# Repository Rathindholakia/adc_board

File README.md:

# adc_board

This is a CadSoft Eagle project of an ADC board using AD7864 for sensing analog input and to interface it with EMIFA of TI OMAP-L137.

Description:

Two AD7864-1 are used for +-10 Vac input

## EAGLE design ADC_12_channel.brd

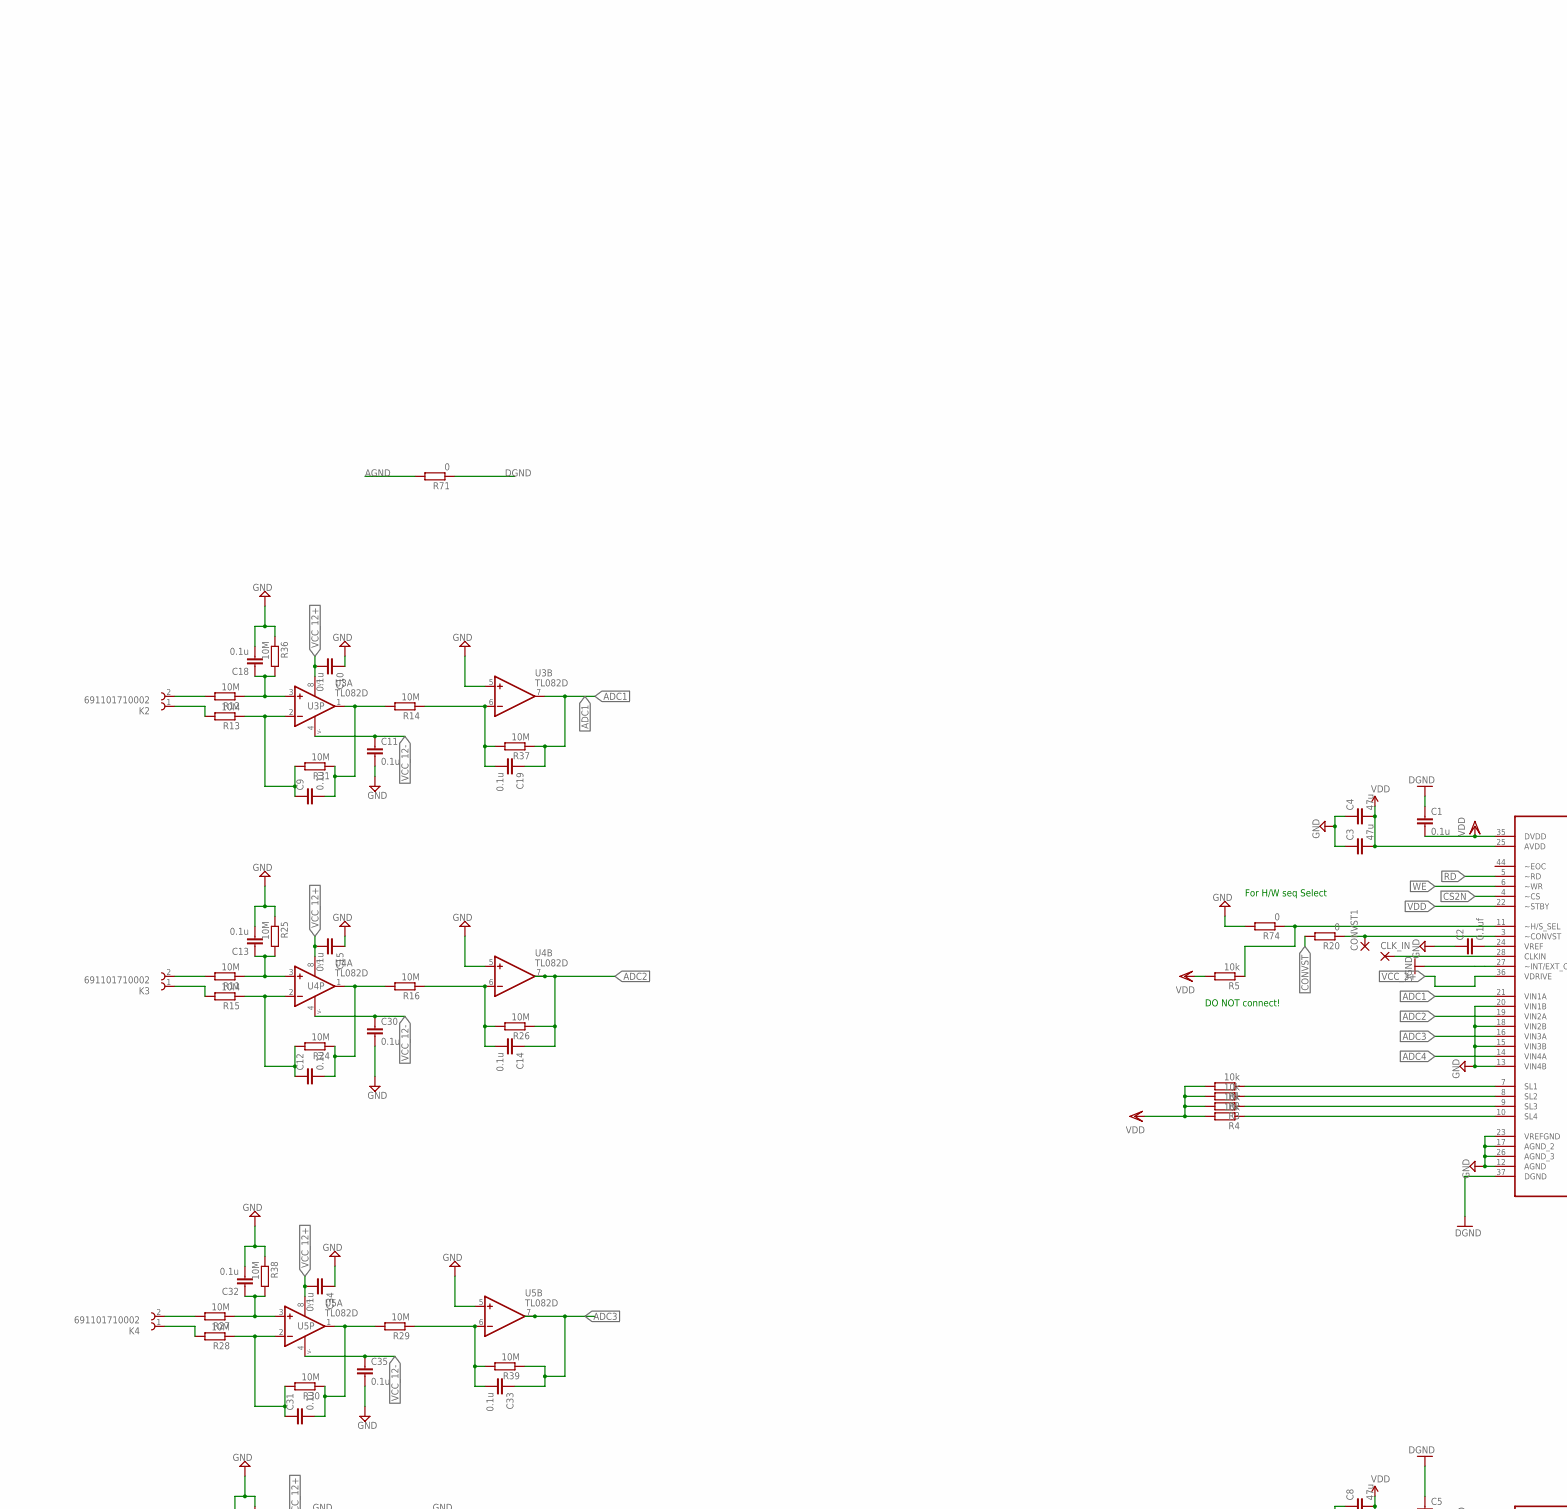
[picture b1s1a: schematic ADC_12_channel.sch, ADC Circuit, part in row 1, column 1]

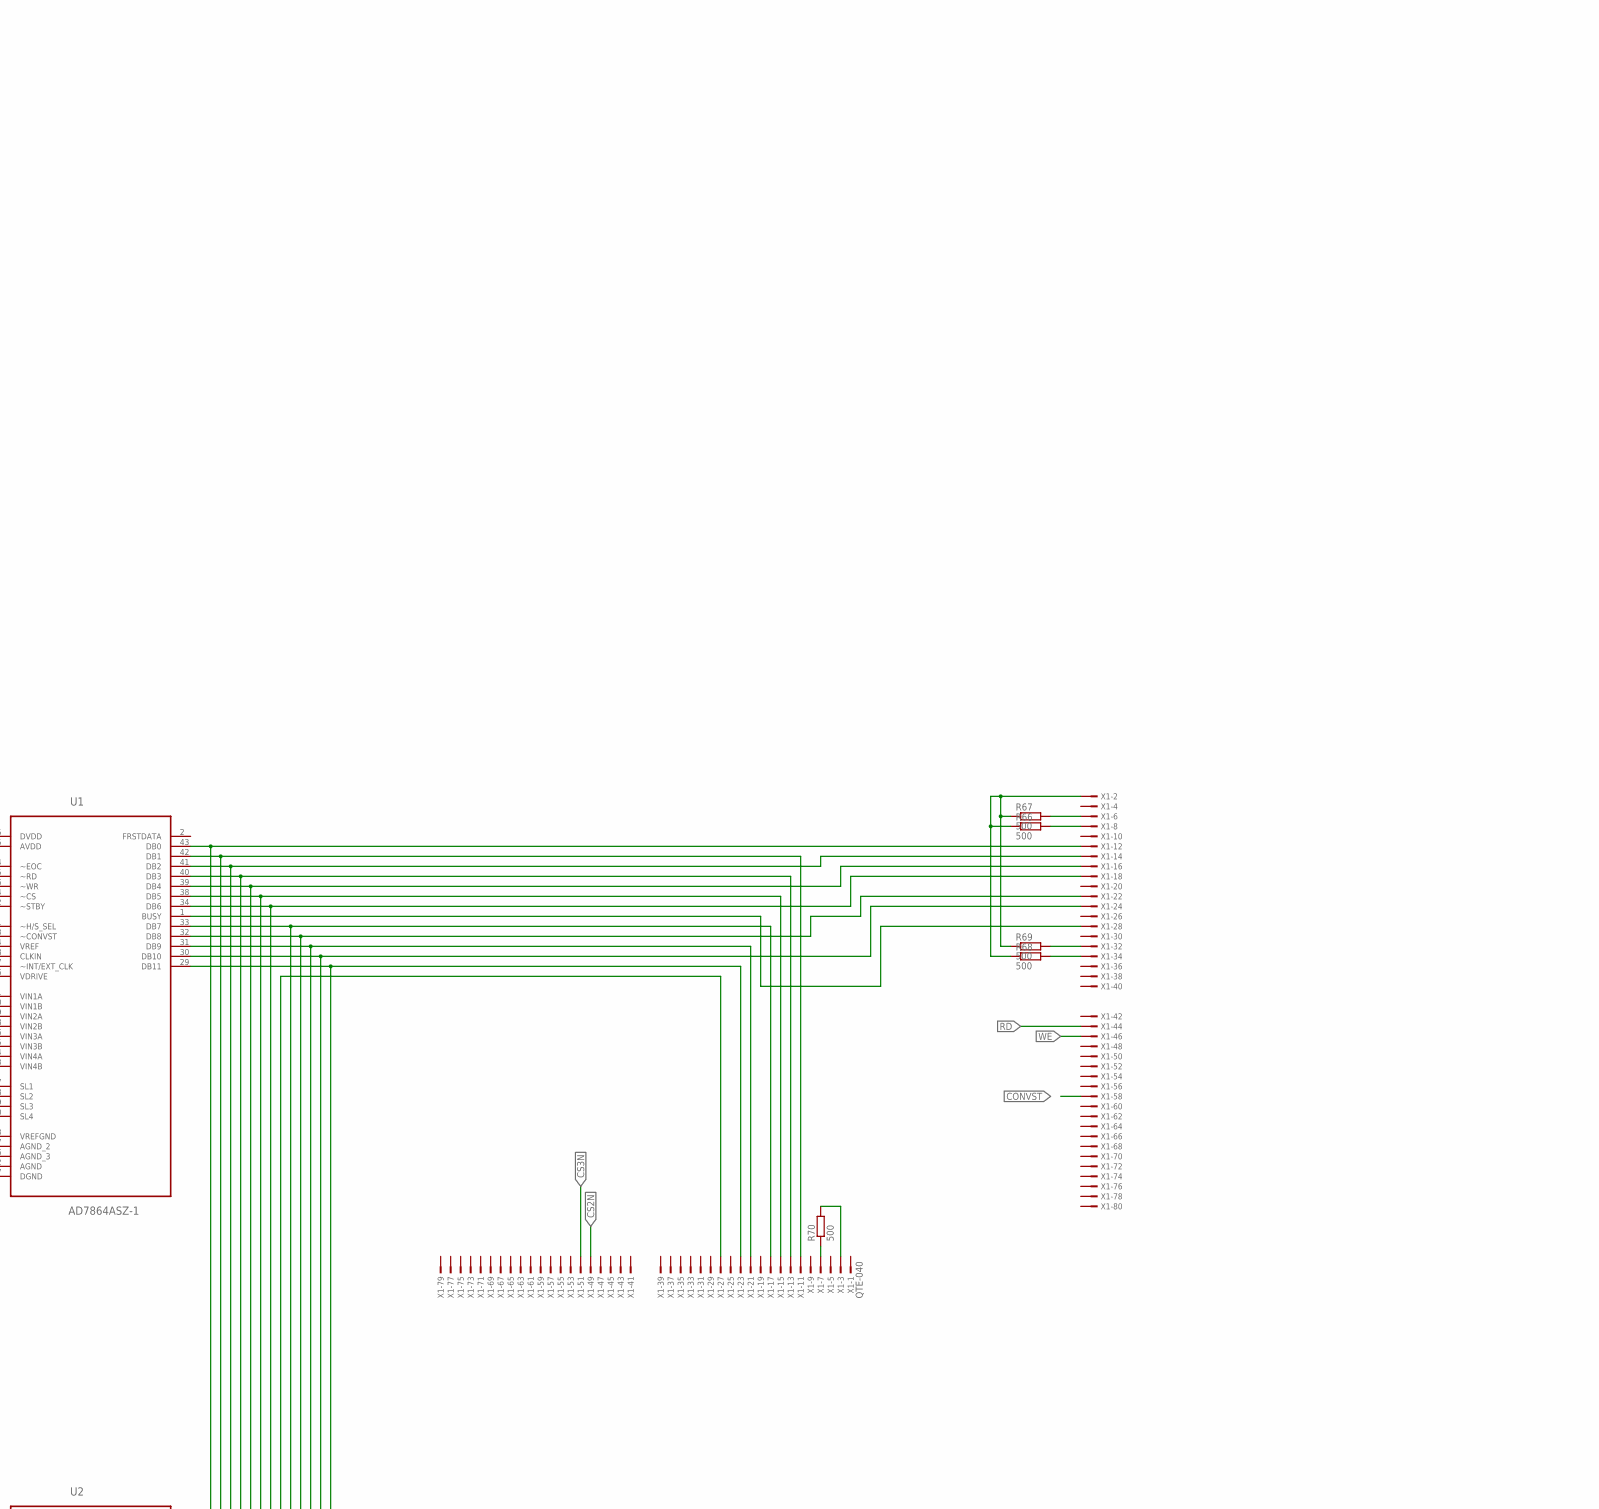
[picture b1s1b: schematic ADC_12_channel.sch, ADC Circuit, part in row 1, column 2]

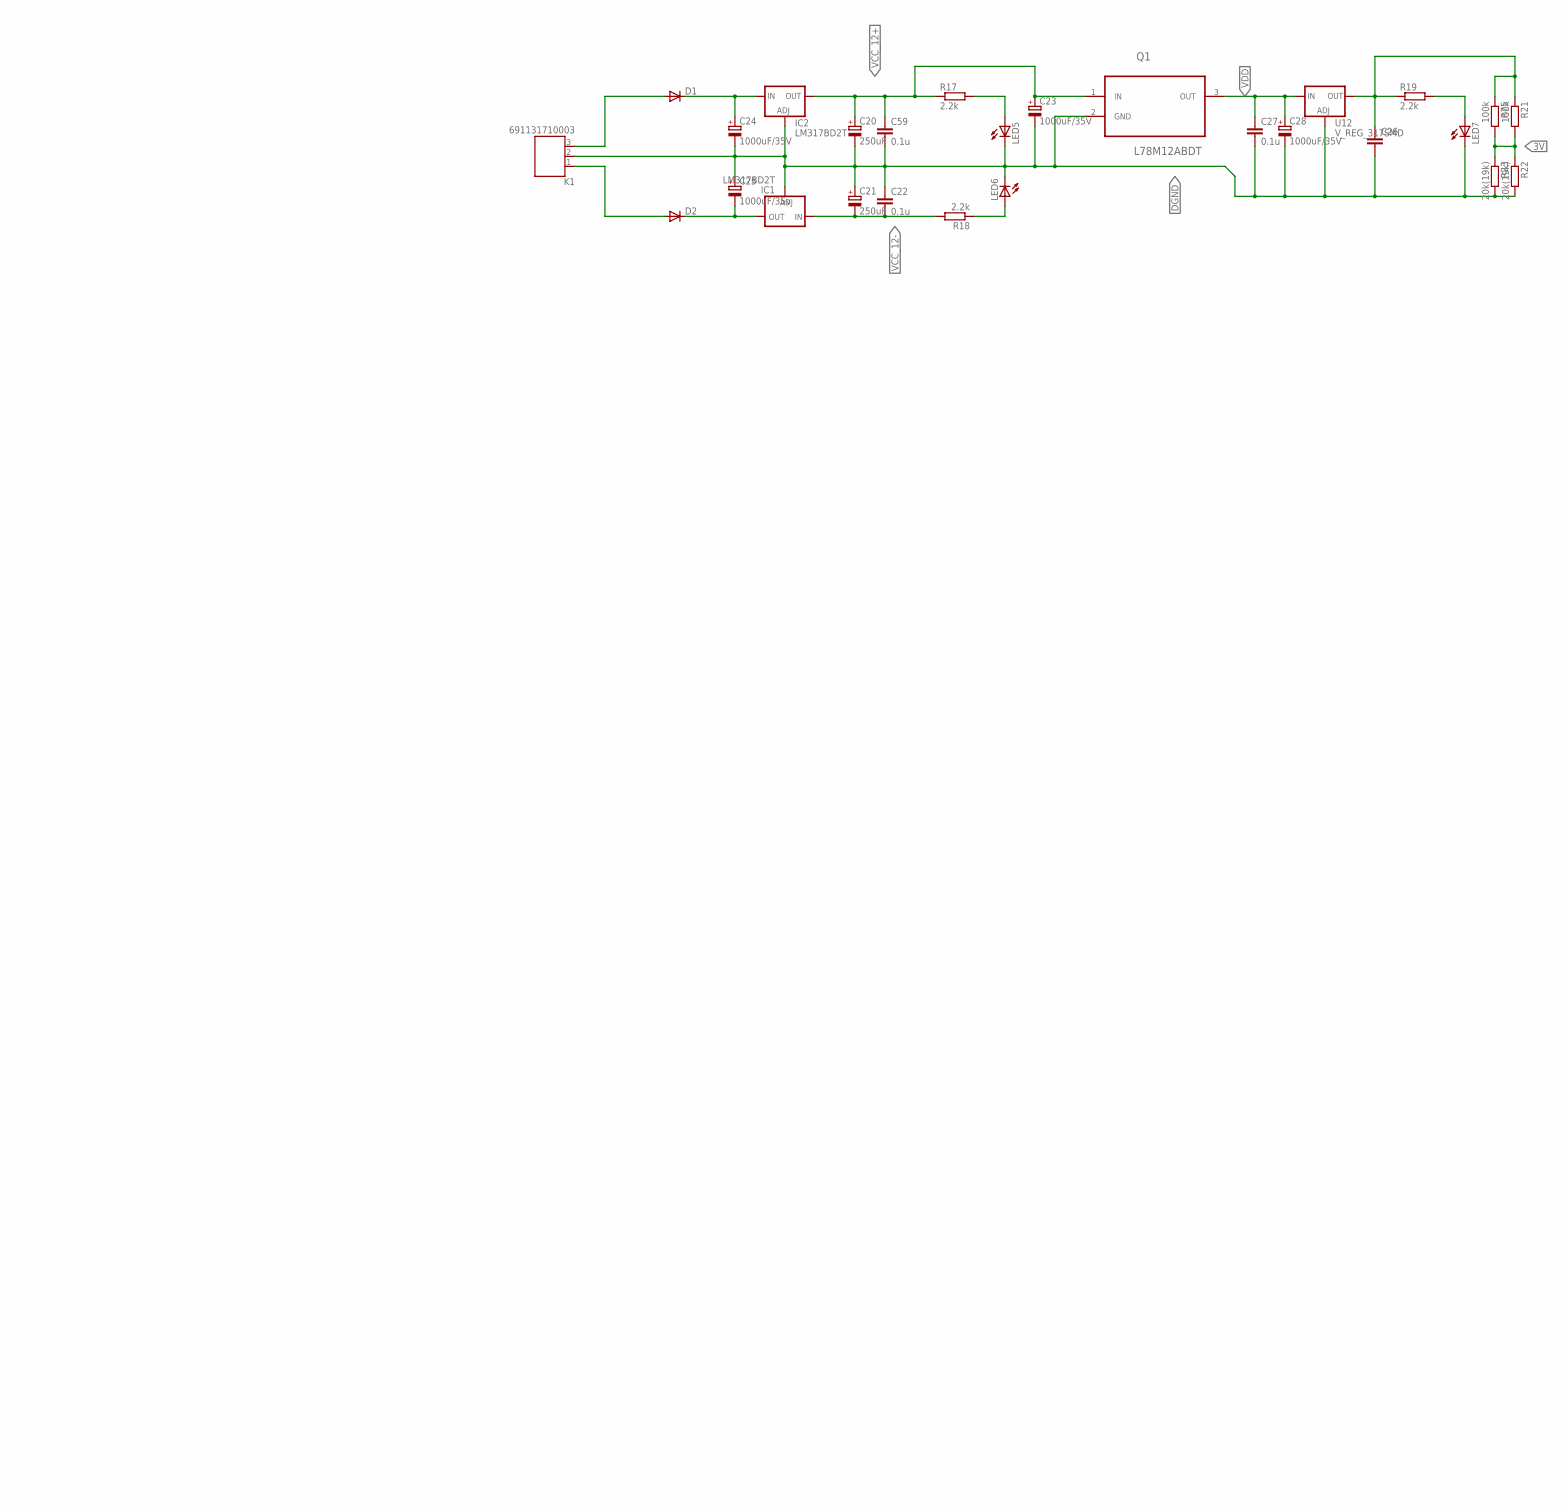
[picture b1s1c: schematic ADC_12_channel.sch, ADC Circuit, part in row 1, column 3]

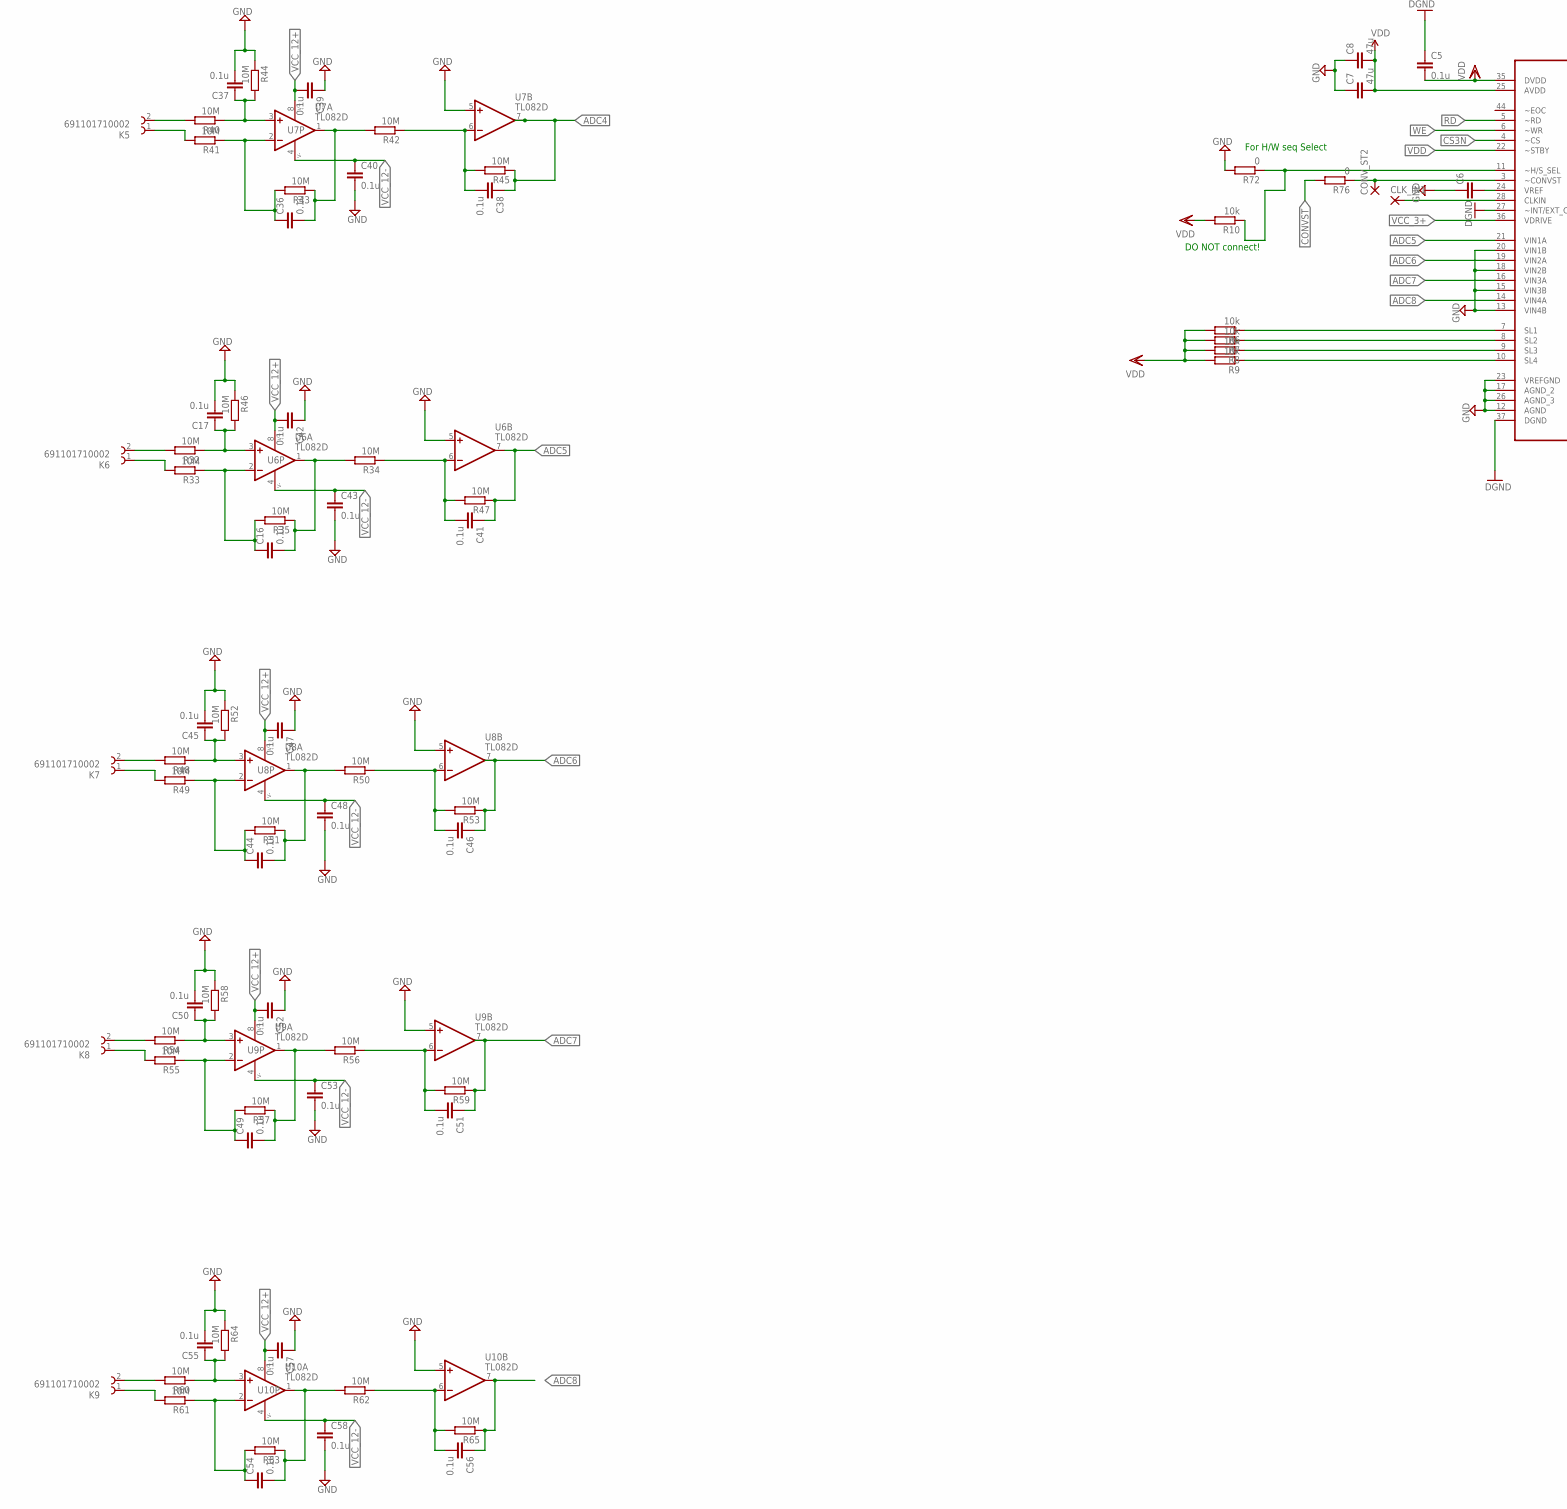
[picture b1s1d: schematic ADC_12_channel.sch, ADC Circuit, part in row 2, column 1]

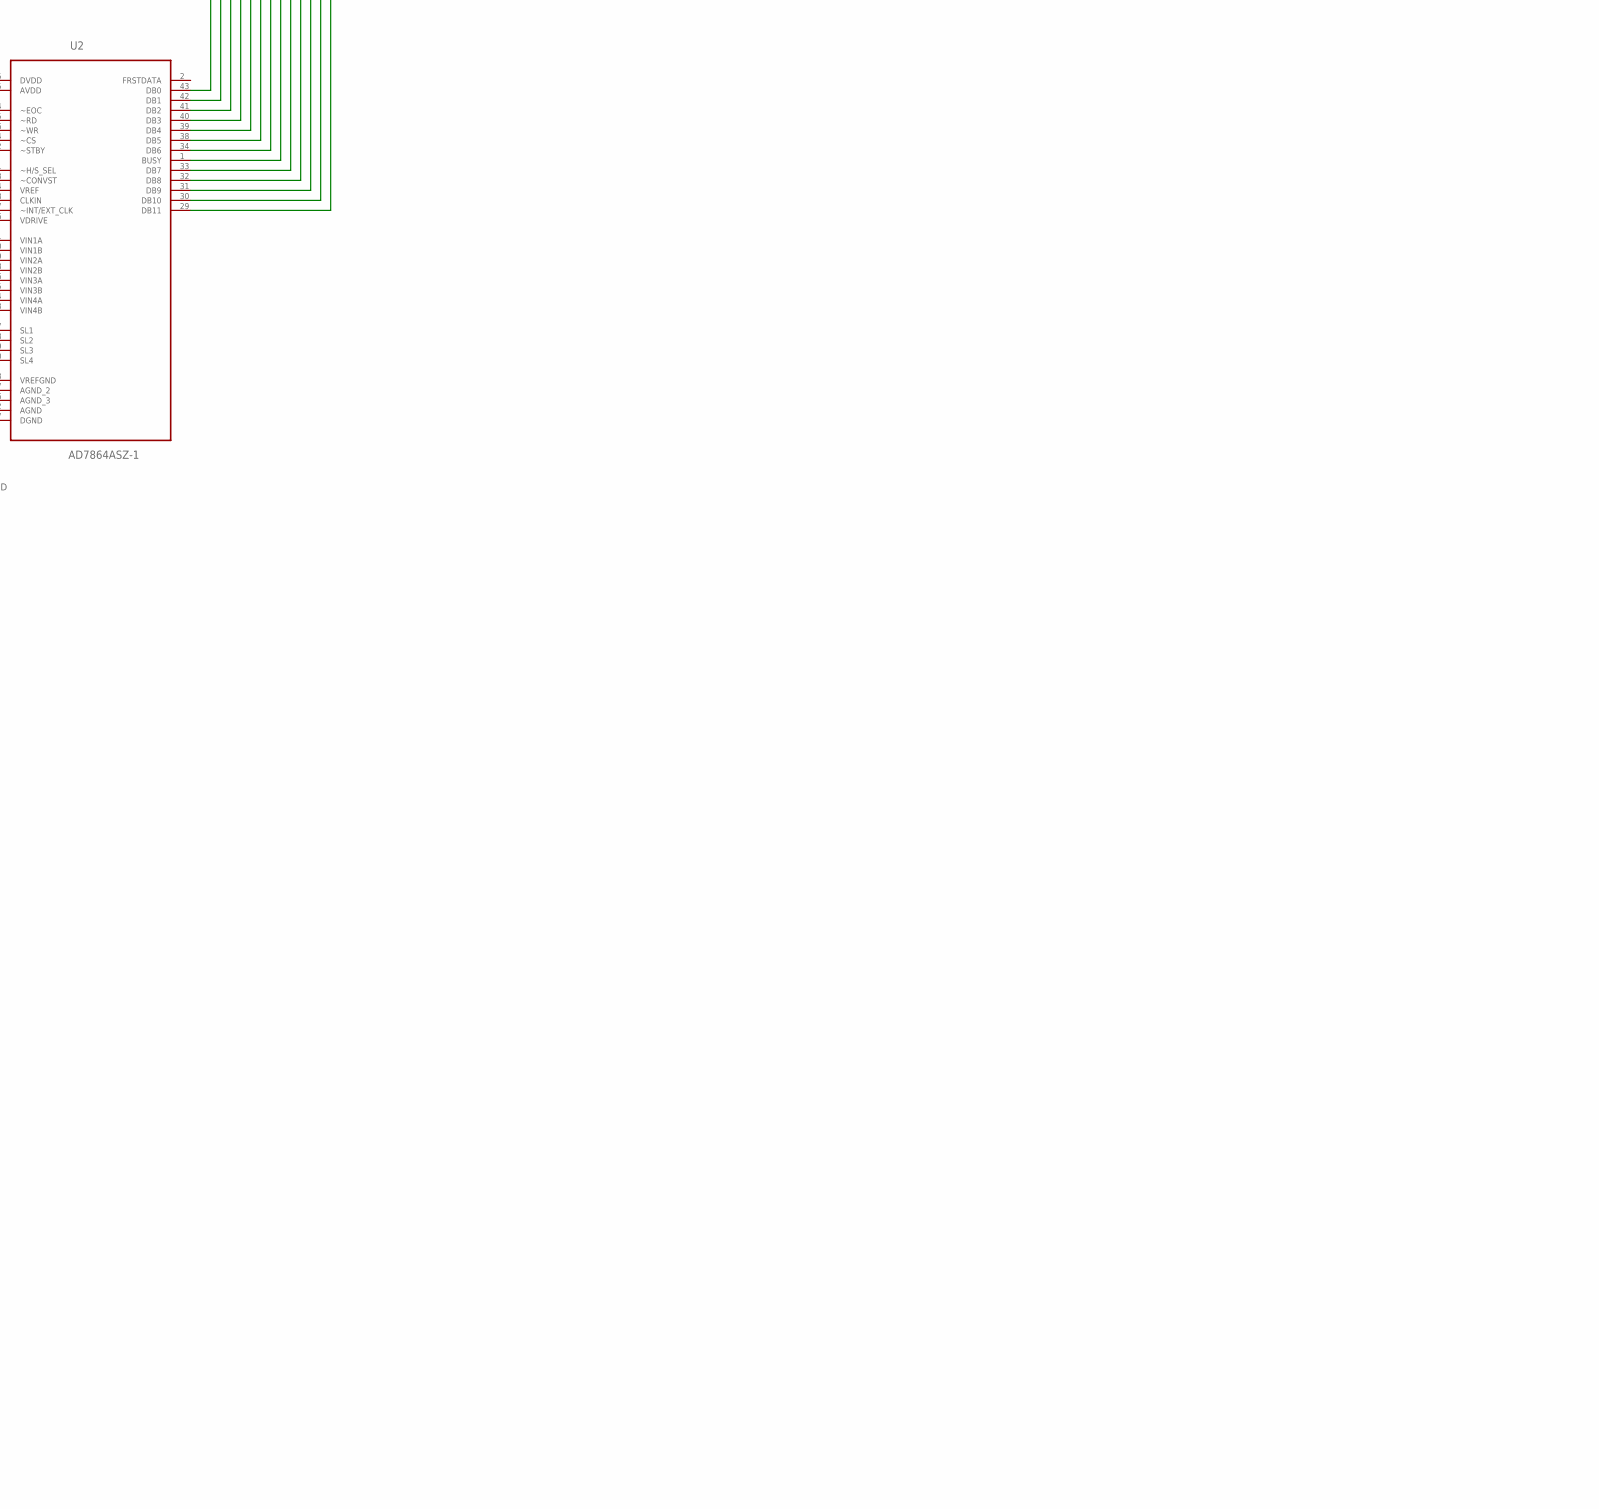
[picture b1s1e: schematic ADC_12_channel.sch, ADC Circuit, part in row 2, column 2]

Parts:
C1, C5, C9, C10, C11, C12, C13, C14, C15, C16, C17, C18, C19, C22, C27, C30, C31, C32, C33, C34, C35, C36, C37, C38, C39, C40, C41, C42, C43, C44, C45, C46, C47, C48, C49, C50, C51, C52, C53, C54, C55, C56, C57, C58, C59: 0.1u; C0603K
C2: 0.1uf; C0603K
C3, C4, C7, C8: 47u; C1206K
C6: C-EUC0603K; C0603K
C20, C21: 250uF; E5-10,5
C23, C24, C28: 1000uF/35V; E5-10,5
C25: 1000uF/35v; E5-10,5
C26: C-EUC1206K; C1206K
CLK_IN, CLK_IN1: 3,17/1,3
CONVST1: 3,17/1,3
CONV_ST2: 3,17/1,3
D1, D2: DIODE-DO-214AC; DO-214AC
IC1, IC2: LM317BD2T; D2PACK
K1: 691131710003
K2, K3, K4, K5, K6, K7, K8, K9: 691101710002
LED5: LEDSML1206; SML1206
LED6, LED7: LEDSMT1206; 1206
Q1: L78M12ABDT; TO225P972X240-3N
R1, R2, R3, R4, R5, R6, R7, R8, R9, R10: 10k; M1206
R11, R12, R13, R14, R15, R16, R24, R25, R26, R27, R28, R29, R30, R31, R32, R33, R34, R35, R36, R37, R38, R39, R40, R41, R42, R43, R44, R45, R47, R48, R49, R50, R51, R53, R54, R55, R56, R57, R59, R60, R61, R62, R63, R64, R65: 10M; M1206
R17, R18, R19: 2.2k; R1206
R20, R71, R72, R74, R76: 0; M1206
R21, R75: 100k; R1206
R22, R23: 20k(19k); R1206
R46, R52, R58: 10M; M0805
R66, R67, R68, R69, R70: 500; M1206
U1, U2: AD7864ASZ-1; QFP80P1390X1390X245-44N
U3, U4, U5, U6, U7, U8, U9, U10: TL082D; SO08
U12: V_REG_317SMD; SOT223
X1: QTE-040

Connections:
3V: R21.2, R22.1, R23.1, R75.2
ADC1: C19.1, R37.1, U1.21 (VIN1A), U3.7 (OUT)
ADC2: C14.1, R26.1, U1.19 (VIN2A), U4.7 (OUT)
ADC3: C33.1, R39.1, U1.16 (VIN3A), U5.7 (OUT)
ADC4: C38.1, R45.1, U1.14 (VIN4A), U7.7 (OUT)
ADC5: C41.1, R47.1, U2.21 (VIN1A), U6.7 (OUT)
ADC6: C46.1, R53.1, U2.19 (VIN2A), U8.7 (OUT)
ADC7: C51.1, R59.1, U2.16 (VIN3A), U9.7 (OUT)
ADC8: C56.1, R65.1, U2.14 (VIN4A), U10.7 (OUT)
AGND: C2.1, C3.1, C4.1, C6.1, C7.1, C8.1, C13.2, C17.2, C18.2, C32.2, C37.2, C45.2, C50.2, C55.2, R25.1, R36.1, R38.1, R44.1, R46.1, R52.1, R58.1, R64.1, R71.2, U1.12 (AGND), U1.13 (VIN4B), U1.15 (VIN3B), U1.17 (AGND_2), U1.18 (VIN2B), U1.20 (VIN1B), U1.23 (VREFGND), U1.26 (AGND_3), U2.12 (AGND), U2.13 (VIN4B), U2.15 (VIN3B), U2.17 (AGND_2), U2.18 (VIN2B), U2.20 (VIN1B), U2.23 (VREFGND), U2.26 (AGND_3), U3.5 (+IN), U4.5 (+IN), U5.5 (+IN), U6.5 (+IN), U7.5 (+IN), U8.5 (+IN), U9.5 (+IN), U10.5 (+IN)
CONVST: R20.2, R76.2, X1.58
CS2N: U1.4 (~CS), X1.49
CS3N: U2.4 (~CS), X1.51
DGND: C1.1, C5.1, C10.1, C11.2, C15.1, C20.-, C21.+, C22.1, C23.-, C24.-, C25.+, C26.2, C27.2, C28.-, C30.2, C34.1, C35.2, C39.1, C40.2, C42.1, C43.2, C47.1, C48.2, C52.1, C53.2, C57.1, C58.2, C59.2, IC1.1 (ADJ), IC2.1 (ADJ), K1.2, LED5.C, LED6.C, LED7.C, Q1.2 (GND), R22.2, R23.2, R71.1, R72.2, R74.2, U1.27 (~INT/EXT_CLK), U1.37 (DGND), U2.27 (~INT/EXT_CLK), U2.37 (DGND), U12.1 (ADJ)
unnamed: U1.43 (DB0), U2.43 (DB0), X1.12
unnamed: C9.1, R13.1, R31.2, U3.2 (-IN)
unnamed: U1.41 (DB2), U2.41 (DB2), X1.14
unnamed: U1.39 (DB4), U2.39 (DB4), X1.16
unnamed: U1.34 (DB6), U2.34 (DB6), X1.18
unnamed: U1.32 (DB8), U2.32 (DB8), X1.22
unnamed: U1.30 (DB10), U2.30 (DB10), X1.24
unnamed: U1.40 (DB3), U2.40 (DB3), X1.13
unnamed: U1.38 (DB5), U2.38 (DB5), X1.15
unnamed: U1.33 (DB7), U2.33 (DB7), X1.17
unnamed: CLK_IN.1, U1.28 (CLKIN)
unnamed: U1.29 (DB11), U2.29 (DB11), X1.23
unnamed: R4.1, U1.10 (SL4)
unnamed: R3.1, U1.9 (SL3)
unnamed: R2.1, U1.8 (SL2)
unnamed: C2.2, U1.24 (VREF)
unnamed: R1.1, U1.7 (SL1)
unnamed: CONVST1.1, R20.1, U1.3 (~CONVST)
unnamed: R5.1, R74.1, U1.11 (~H/S_SEL)
unnamed: R9.1, U2.10 (SL4)
unnamed: R8.1, U2.9 (SL3)
unnamed: R7.1, U2.8 (SL2)
unnamed: R6.1, U2.7 (SL1)
unnamed: C6.2, U2.24 (VREF)
unnamed: CONV_ST2.1, R76.1, U2.3 (~CONVST)
unnamed: R10.1, R72.1, U2.11 (~H/S_SEL)
unnamed: U1.42 (DB1), U2.42 (DB1), X1.11
unnamed: K3.2, R11.2
unnamed: C19.2, R14.1, R37.2, U3.6 (-IN)
unnamed: U1.31 (DB9), U2.31 (DB9), X1.21
unnamed: K3.1, R15.2
unnamed: K2.1, R13.2
unnamed: C12.1, R15.1, R24.2, U4.2 (-IN)
unnamed: C12.2, R16.2, R24.1, U4.1 (OUT)
unnamed: C25.-, D2.C, IC1.3 (OUT)
unnamed: C24.+, D1.C, IC2.2 (IN)
unnamed: LED5.A, R17.2
unnamed: LED6.A, R18.1
unnamed: D1.A, K1.3
unnamed: D2.A, K1.1
unnamed: LED7.A, R19.2
unnamed: K6.2, R32.2
unnamed: K6.1, R33.2
unnamed: C13.1, R11.1, R25.2, U4.3 (+IN)
unnamed: C14.2, R16.1, R26.2, U4.6 (-IN)
unnamed: CLK_IN1.1, U2.28 (CLKIN)
unnamed: U1.1 (BUSY), X1.28
unnamed: U2.1 (BUSY), X1.27
unnamed: K4.2, R27.2
unnamed: K2.2, R12.2
unnamed: C18.1, R12.1, R36.2, U3.3 (+IN)
unnamed: C9.2, R14.2, R31.1, U3.1 (OUT)
unnamed: K4.1, R28.2
unnamed: C31.1, R28.1, R30.2, U5.2 (-IN)
unnamed: C31.2, R29.2, R30.1, U5.1 (OUT)
unnamed: C32.1, R27.1, R38.2, U5.3 (+IN)
unnamed: C16.1, R33.1, R35.2, U6.2 (-IN)
unnamed: C16.2, R34.2, R35.1, U6.1 (OUT)
unnamed: C17.1, R32.1, R46.2, U6.3 (+IN)
unnamed: C41.2, R34.1, R47.2, U6.6 (-IN)
unnamed: C33.2, R29.1, R39.2, U5.6 (-IN)
unnamed: K5.2, R40.2
unnamed: K5.1, R41.2
unnamed: C36.1, R41.1, R43.2, U7.2 (-IN)
unnamed: C36.2, R42.2, R43.1, U7.1 (OUT)
unnamed: C37.1, R40.1, R44.2, U7.3 (+IN)
unnamed: C38.2, R42.1, R45.2, U7.6 (-IN)
unnamed: K7.2, R48.2
unnamed: K7.1, R49.2
unnamed: C44.1, R49.1, R51.2, U8.2 (-IN)
unnamed: C44.2, R50.2, R51.1, U8.1 (OUT)
unnamed: C45.1, R48.1, R52.2, U8.3 (+IN)
unnamed: C46.2, R50.1, R53.2, U8.6 (-IN)
unnamed: K8.2, R54.2
unnamed: K8.1, R55.2
unnamed: C49.1, R55.1, R57.2, U9.2 (-IN)
unnamed: C49.2, R56.2, R57.1, U9.1 (OUT)
unnamed: C50.1, R54.1, R58.2, U9.3 (+IN)
unnamed: C51.2, R56.1, R59.2, U9.6 (-IN)
unnamed: K9.2, R60.2
unnamed: K9.1, R61.2
unnamed: C54.1, R61.1, R63.2, U10.2 (-IN)
unnamed: C54.2, R62.2, R63.1, U10.1 (OUT)
unnamed: C55.1, R60.1, R64.2, U10.3 (+IN)
unnamed: C56.2, R62.1, R65.2, U10.6 (-IN)
unnamed: R66.1, R67.1, R68.1, R69.1, X1.2
unnamed: R67.2, X1.6
unnamed: R66.2, X1.8
unnamed: R69.2, X1.32
unnamed: R68.2, X1.34
unnamed: R70.2, X1.3
unnamed: R70.1, X1.7
RD: U1.5 (~RD), U2.5 (~RD), X1.44
VCC_3+: U1.36 (VDRIVE), U2.36 (VDRIVE)
VCC_5+: C26.1, R19.1, R21.1, R75.1, U12.2 (OUT)
VCC_12+: C10.2, C15.2, C20.+, C23.+, C34.2, C39.2, C42.2, C47.2, C52.2, C57.2, C59.1, IC2.3 (OUT), Q1.1 (IN), R17.1, U3.8 (V+), U4.8 (V+), U5.8 (V+), U6.8 (V+), U7.8 (V+), U8.8 (V+), U9.8 (V+), U10.8 (V+)
VCC_12-: C11.1, C21.-, C22.2, C30.1, C35.1, C40.1, C43.1, C48.1, C53.1, C58.1, IC1.2 (IN), R18.2, U3.4 (V-), U4.4 (V-), U5.4 (V-), U6.4 (V-), U7.4 (V-), U8.4 (V-), U9.4 (V-), U10.4 (V-)
VDD: C1.2, C3.2, C4.2, C5.2, C7.2, C8.2, C27.1, C28.+, Q1.3 (OUT), R1.2, R2.2, R3.2, R4.2, R5.2, R6.2, R7.2, R8.2, R9.2, R10.2, U1.22 (~STBY), U1.25 (AVDD), U1.35 (DVDD), U2.22 (~STBY), U2.25 (AVDD), U2.35 (DVDD), U12.3 (IN)
WE: U1.6 (~WR), U2.6 (~WR), X1.46

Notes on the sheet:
For H/W seq Select
DO NOT connect!

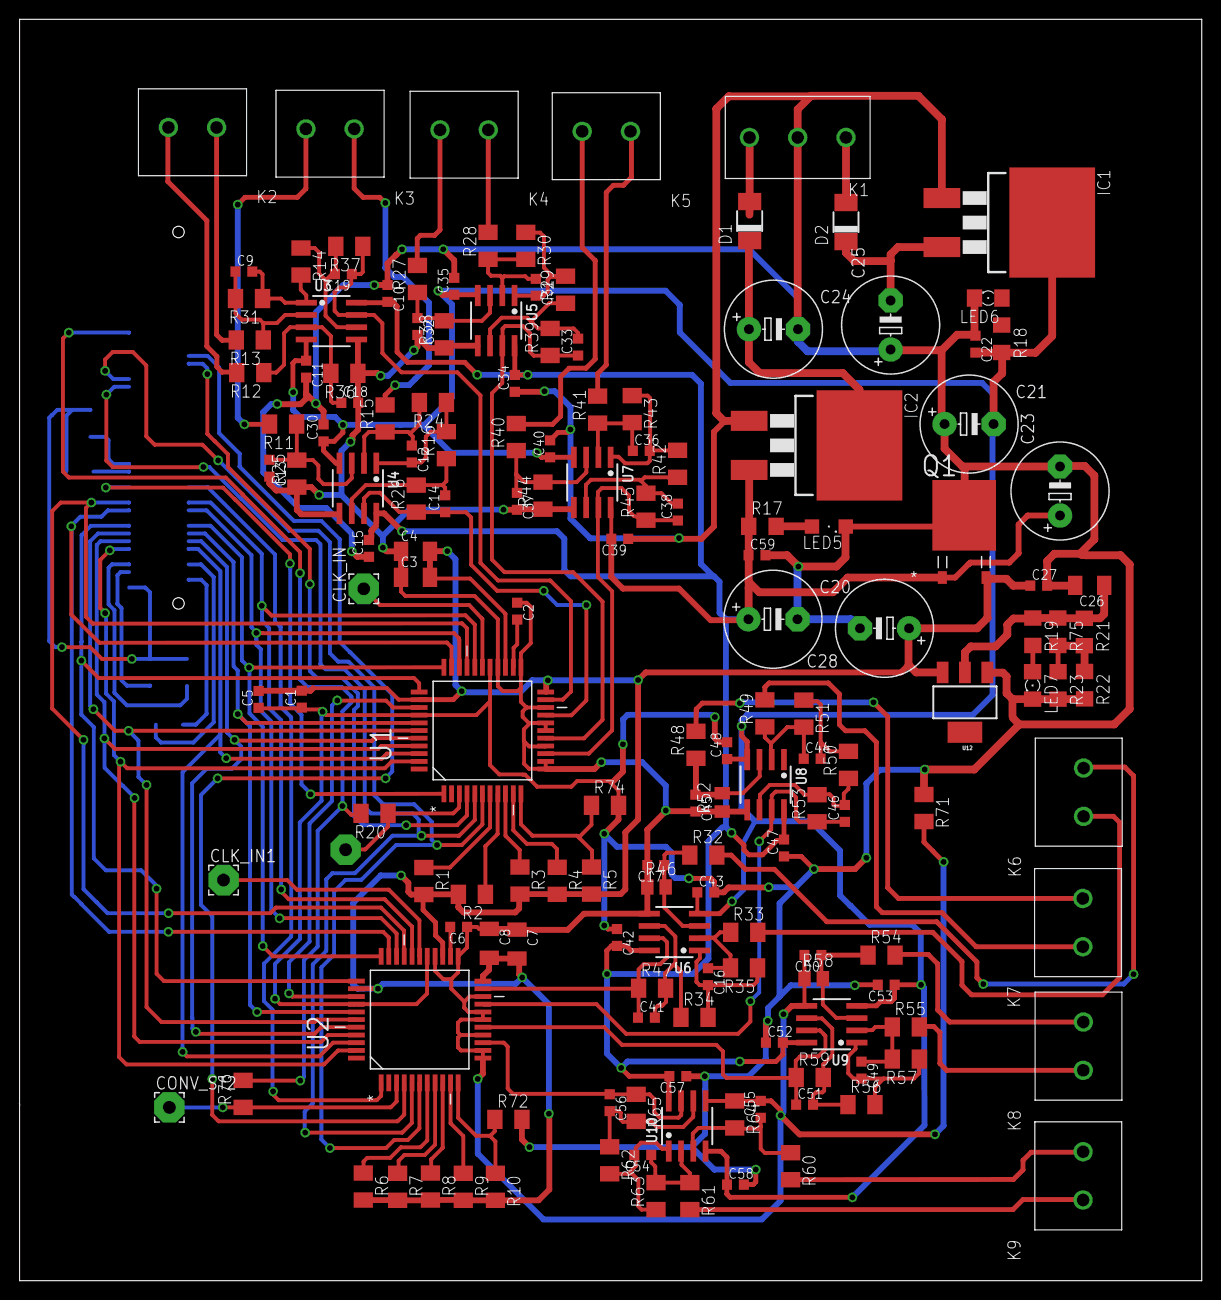
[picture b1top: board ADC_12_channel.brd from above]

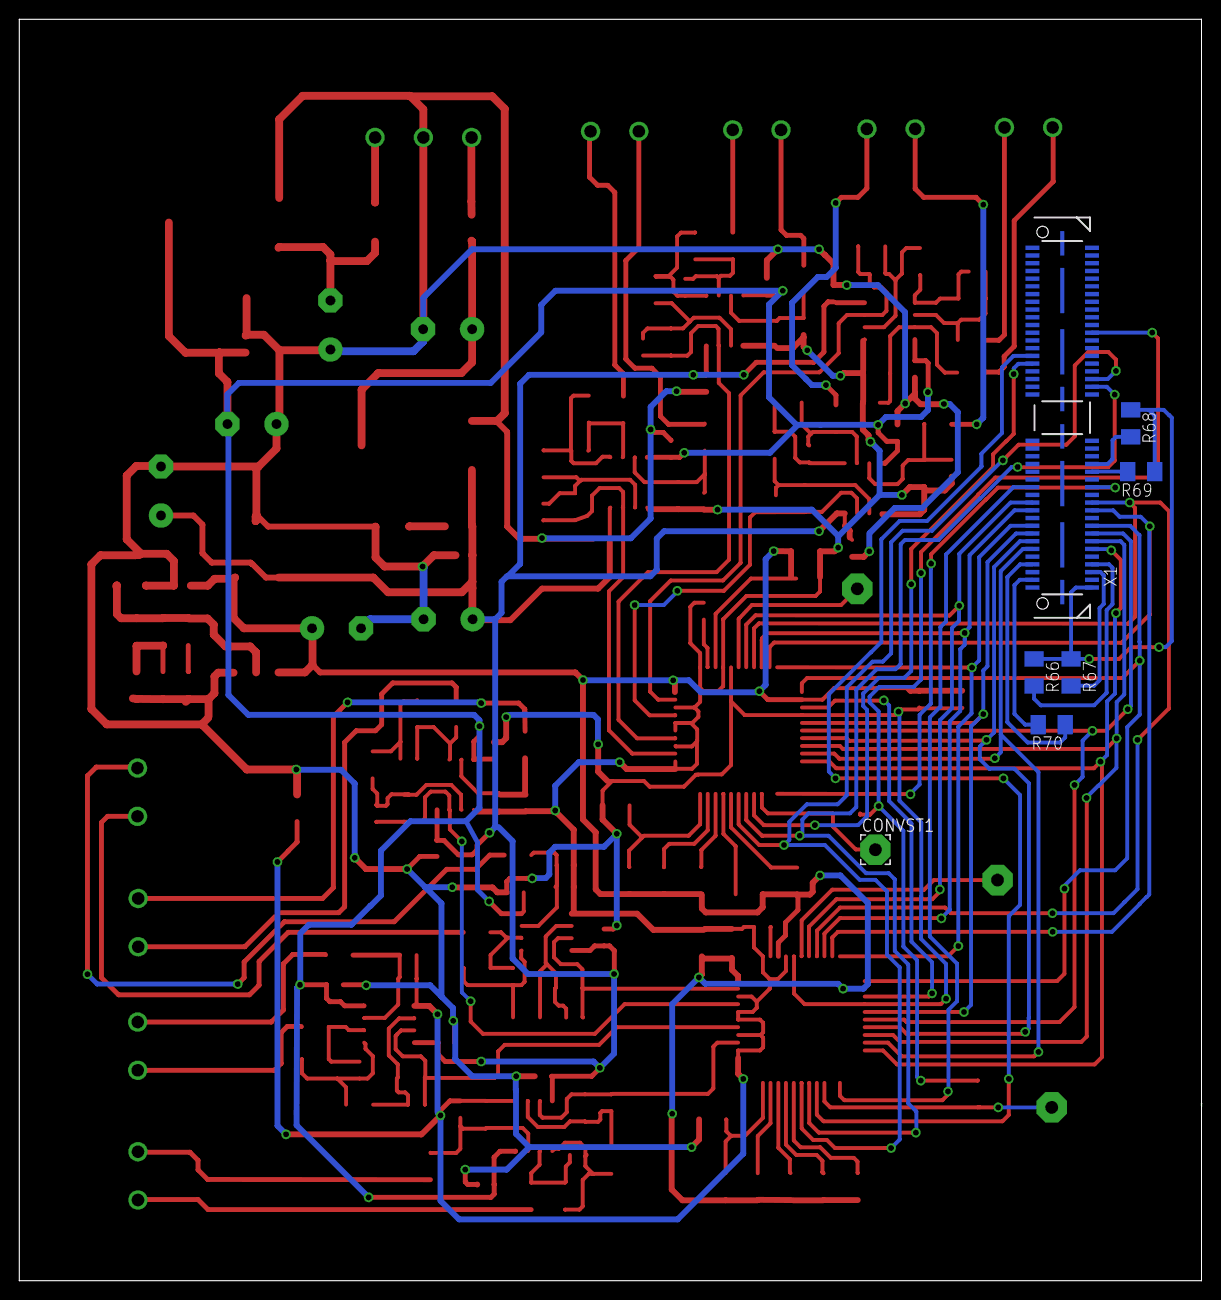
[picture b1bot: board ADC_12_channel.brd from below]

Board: 2 copper layers, 122.5 x 130.7 mm, 166 parts (7 on the bottom side), 113 nets.

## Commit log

2016-10-07 Starting the project on Git
    Schematic is already done, preliminary PCB routing done.
    Known issues:
    1) Supply's LDO IC are still not confirmed
    2) AGND & DGND are seperate and their' connection is bit doubtful
    3) DVdd - AVdd are also connected togather.
    Thought of Git Repo creation came afterwards so no versions before this :)
2016-10-07 Create README.md
    Added Description
2016-10-07 Routed 4 OpAmp stages for 1st ADC chip
2016-10-07 Added CLK INT/EXT resistor & relocated inout Opamp
    Reducing the size
    created possibility to input external clock
    relocated the Omapms to reduce the board size.
2016-10-22 Removed unnecessary component Adjusted the location of ADC opamps Realigned Processors!! Very criticall
2016-10-22 Removed Isolating 0 ohm resistors..
    End of session commit
2016-10-22 End of session Commit
    Moved ADC-1 to further right
    Layed remaining Data bit
    Layed busy bit
    Removed int/ext clock signal resistor
2016-10-24 Commit before major revision (A restore point!) rearranging ADC input opamps to a borld position
2016-10-24 Restore pint - 2 Moved ADC chip connected the two resistors
2016-10-27 Added a voltage divider for 3V supply corrected the VDD and AVDD mess-up
2016-11-04 Supply sorting commit
    Sorted I/p +- 12V supply, 5V pending
    changed Resistor package from 0805 to 1206 because its cheap, easy to handle, and easyly available
    Update of R package done for 1st two input channels
2016-11-07 R & C package update
    Updated all R to 1206
    Updated all input stage C of 0.1u to 0603 package
    All 47uF to 1206 package
2016-11-09 Supply Finally sorted out!
    arranging supply components
    Working on realigning resistors of input stage
2016-11-10 Layout of Supply DONE!
2016-11-10 Conversion ST signal, supply & area
    -Added isolating resistor in CONVST signal coming from header/processor
    -Defined boundry of the baord
    - Relocated and reorianted the supply
2016-11-11 ADC-1 Opamp component arrangement FINALIZED!
    Uniformly arranged all component of Opamps 1-4
2016-11-11 ADC-2 Opamp layout over
2016-11-22 Routed ADC1 to header, ADC1 to ADC2
2016-11-23 Finished connections to header
2016-11-24 Connected ADC2 with header Relocated ADC2 towards right
    came to know about the VDD DVDD issue! and missing of 5v supply,
    will be resolved in next commit
2016-12-04 Added 5v stage (for Vdd & DVdd)
    Finally fixed the supply now. Only, taking out the 12v, 5v and 3v points remaining.
2016-12-04 joined AVdd and DVdd
    It was of no use, due to lack of two seperate regulator IC.
    reduced component and simplified the circuit.
2016-12-05 Re-arranged ADC1 opamps
    Filled up the gap around the header,
    jigsawed them for proper space usage.
    Next commit ADC1 peripheral components
2016-12-05 Finished all peripherals of ADC1
2016-12-06 Arranged & Connected ADC2 opamps
    Arranged & connected ADC2 opampms
    Arranged & connected i/p header for ADC1 opamps
2016-12-06 arranged & connected ADC2 headers
    Routed +12_VCC
    Routed VDD
2016-12-07 Connected -12_Vdd and +5 V
2016-12-07 Added isolating resistor between DGND & AGND
    Layed VDD, DVDD tracks.
    Created AGND plane
2016-12-08 DGND plane complete
    Rearranged the Vdd resistors
2016-12-08 Finished routing and eleminating DRCs
    Final Sanity check remaining
2016-12-13 Finished Ground plane and supply
2017-01-02 border adjustments

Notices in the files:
parts and their libraries:
Wurth_Elektronik_Electromechanic_Termina: Copyright: Würth Elektronik
op-amp: Copyright (C) 2006 by Bob Starr
SparkFun-PowerIC: Licensing: Creative Commons ShareAlike 4.0 International - https://creativecommons.org/licenses/by-sa/4.0
